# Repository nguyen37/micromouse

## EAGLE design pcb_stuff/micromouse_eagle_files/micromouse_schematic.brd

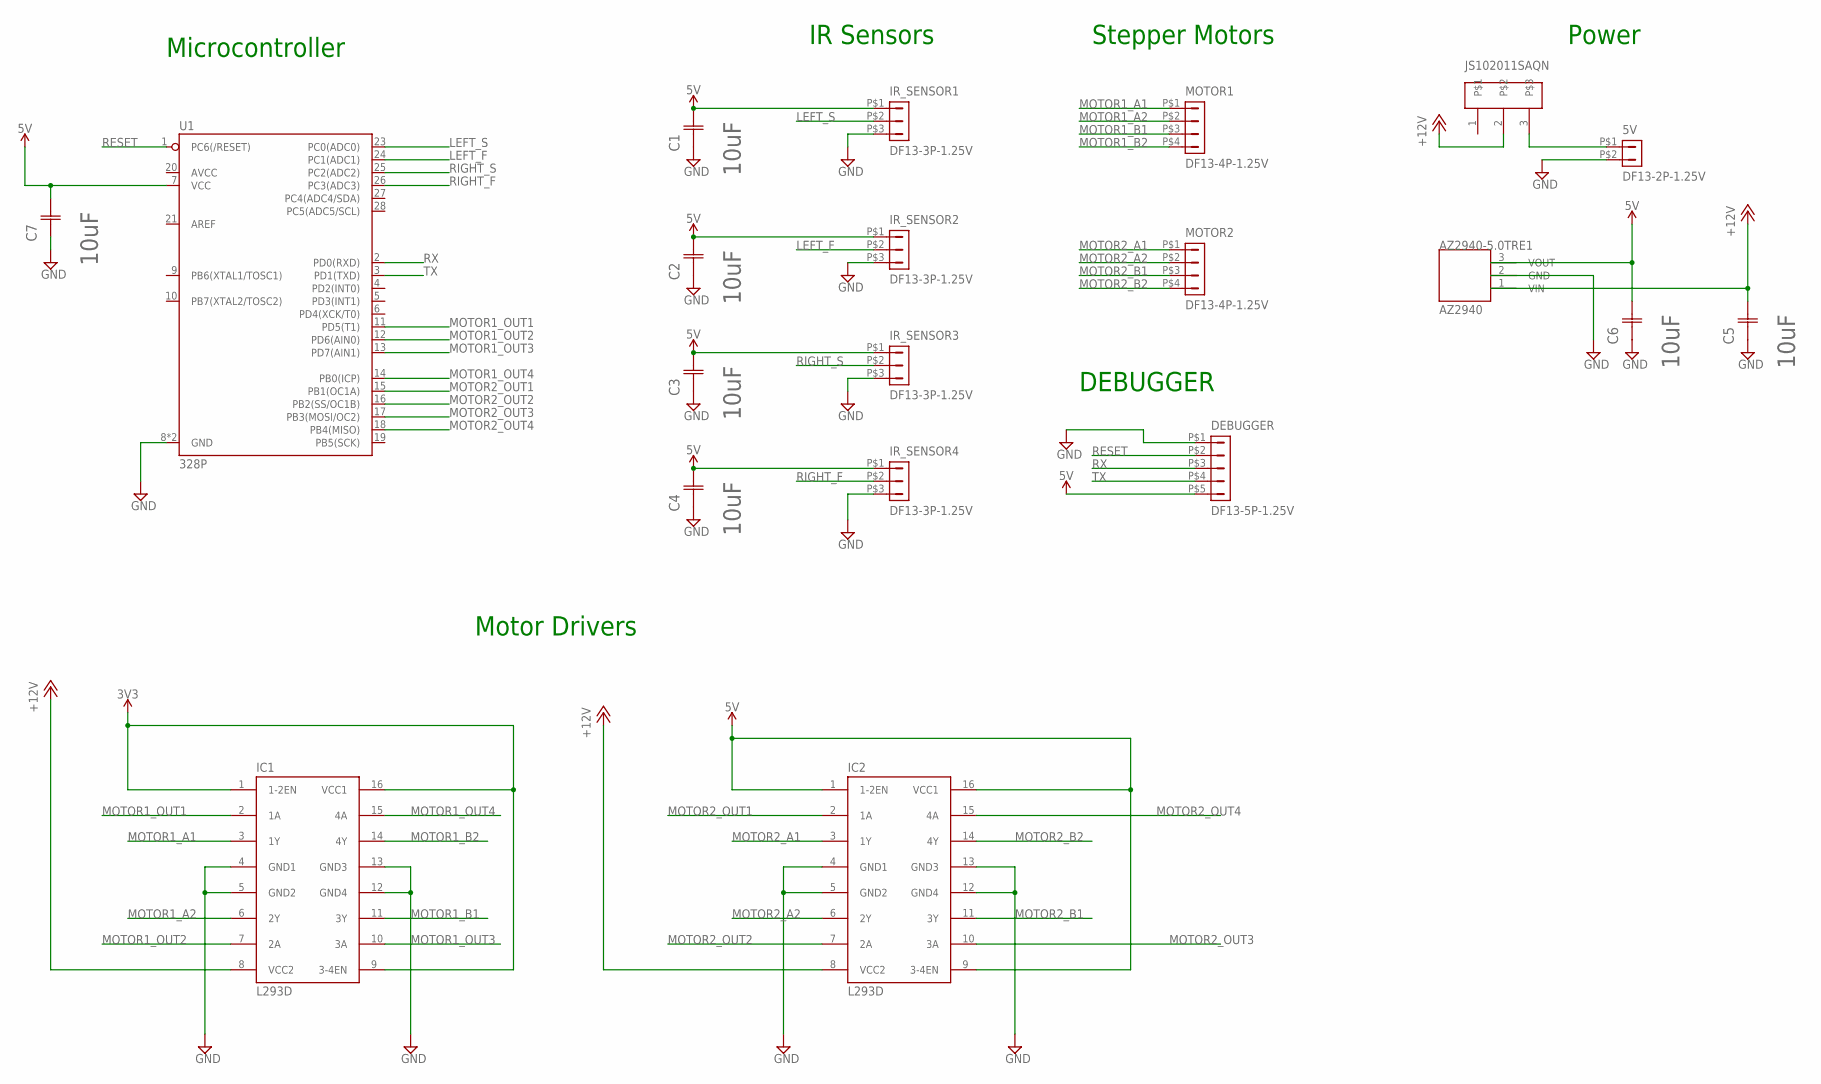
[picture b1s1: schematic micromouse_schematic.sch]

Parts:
5V: DF13-2P-1.25V; DF13C-2P-1.25V
AZ2940-5.0TRE1: AZ2940; TO-252
C1, C2, C3, C4, C5, C6, C7: 10uF; CAPC2013X135N
DEBUGGER: DF13-5P-1.25V; DF13C-5P-1.25V
IC1, IC2: L293D; DIL16
IR_SENSOR1, IR_SENSOR2, IR_SENSOR3, IR_SENSOR4: DF13-3P-1.25V; DF13C-3P-1.25V
JS102011SAQN: JS102011SAQN
MOTOR1, MOTOR2: DF13-4P-1.25V; DF13C-4P-1.25V
U1: 328P; DIP28

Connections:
+12V: AZ2940-5.0TRE1.1 (VIN), C5.2 (C2), IC1.8 (VCC2), IC2.8 (VCC2), JS102011SAQN.2
GND: 5V.P$2 (2), AZ2940-5.0TRE1.2 (GND), C1.1 (C1), C2.1 (C1), C3.1 (C1), C4.1 (C1), C5.1 (C1), C6.1 (C1), C7.1 (C1), DEBUGGER.P$1 (1), IC1.4 (GND1), IC1.5 (GND2), IC1.12 (GND4), IC1.13 (GND3), IC2.4 (GND1), IC2.5 (GND2), IC2.12 (GND4), IC2.13 (GND3), IR_SENSOR1.P$3 (3), IR_SENSOR2.P$3 (3), IR_SENSOR3.P$3 (3), IR_SENSOR4.P$3 (3), U1.8 (GND), U1.22 (GND)
LEFT_F: IR_SENSOR2.P$2 (2), U1.24 (PC1(ADC1))
LEFT_S: IR_SENSOR1.P$2 (2), U1.23 (PC0(ADC0))
MOTOR1_A1: IC1.3 (1Y), MOTOR1.P$1 (1)
MOTOR1_A2: IC1.6 (2Y), MOTOR1.P$2 (2)
MOTOR1_B1: IC1.11 (3Y), MOTOR1.P$3 (3)
MOTOR1_B2: IC1.14 (4Y), MOTOR1.P$4 (4)
MOTOR1_OUT1: IC1.2 (1A), U1.11 (PD5(T1))
MOTOR1_OUT2: IC1.7 (2A), U1.12 (PD6(AIN0))
MOTOR1_OUT3: IC1.10 (3A), U1.13 (PD7(AIN1))
MOTOR1_OUT4: IC1.15 (4A), U1.14 (PB0(ICP))
MOTOR2_A1: IC2.3 (1Y), MOTOR2.P$1 (1)
MOTOR2_A2: IC2.6 (2Y), MOTOR2.P$2 (2)
MOTOR2_B1: IC2.11 (3Y), MOTOR2.P$3 (3)
MOTOR2_B2: IC2.14 (4Y), MOTOR2.P$4 (4)
MOTOR2_OUT1: IC2.2 (1A), U1.15 (PB1(OC1A))
MOTOR2_OUT2: IC2.7 (2A), U1.16 (PB2(SS/OC1B))
MOTOR2_OUT3: IC2.10 (3A), U1.17 (PB3(MOSI/OC2))
MOTOR2_OUT4: IC2.15 (4A), U1.18 (PB4(MISO))
unnamed: 5V.P$1 (1), JS102011SAQN.3
RESET: DEBUGGER.P$2 (2), U1.1 (PC6(/RESET))
RIGHT_F: IR_SENSOR4.P$2 (2), U1.26 (PC3(ADC3))
RIGHT_S: IR_SENSOR3.P$2 (2), U1.25 (PC2(ADC2))
RX: DEBUGGER.P$3 (3), U1.2 (PD0(RXD))
TX: DEBUGGER.P$4 (4), U1.3 (PD1(TXD))
VCC: AZ2940-5.0TRE1.3 (VOUT), C1.2 (C2), C2.2 (C2), C3.2 (C2), C4.2 (C2), C6.2 (C2), C7.2 (C2), DEBUGGER.P$5 (5), IC1.1 (1-2EN), IC1.9 (3-4EN), IC1.16 (VCC1), IC2.1 (1-2EN), IC2.9 (3-4EN), IC2.16 (VCC1), IR_SENSOR1.P$1 (1), IR_SENSOR2.P$1 (1), IR_SENSOR3.P$1 (1), IR_SENSOR4.P$1 (1), U1.7 (VCC)

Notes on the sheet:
Stepper Motors
IR Sensors
DEBUGGER
Microcontroller
Motor Drivers
Power

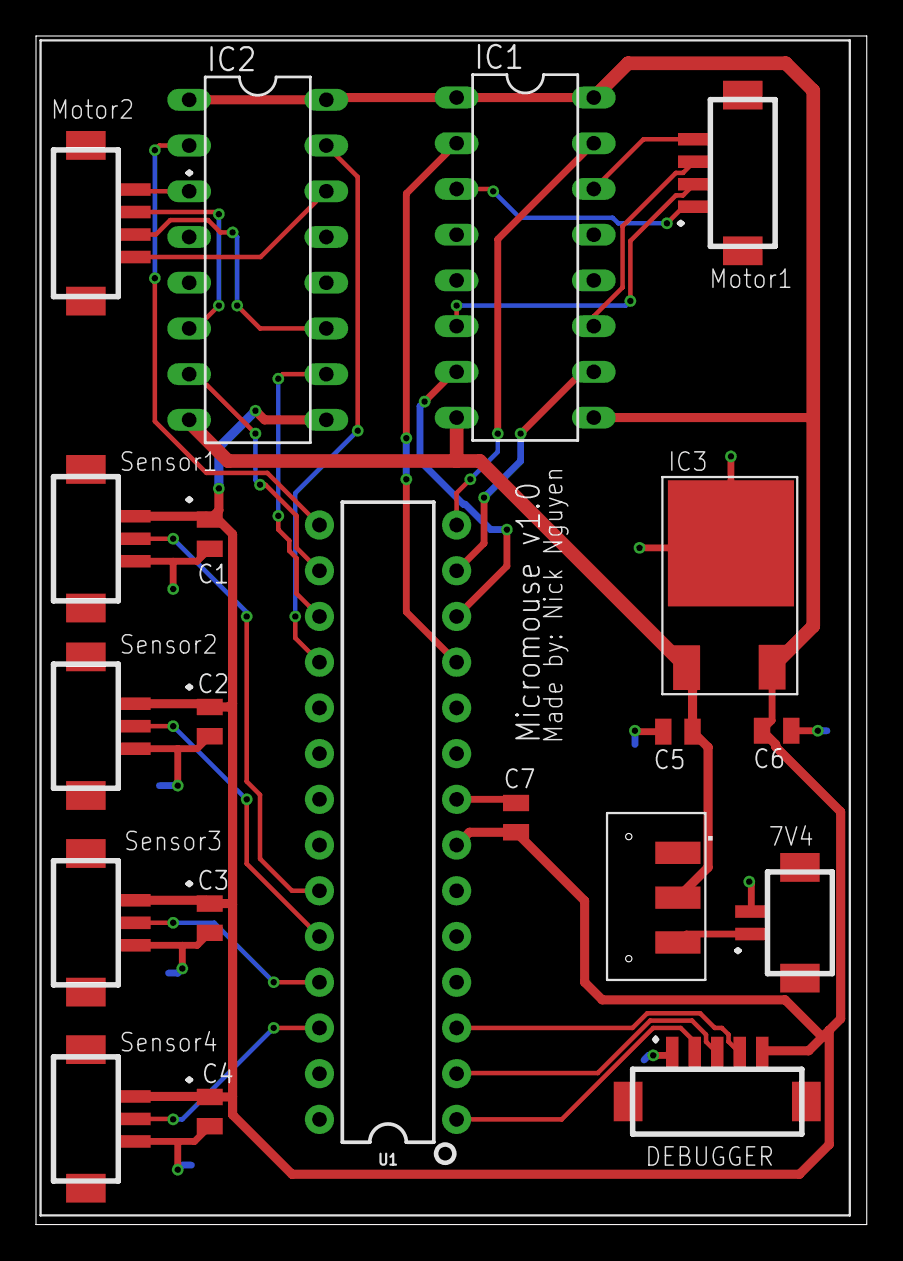
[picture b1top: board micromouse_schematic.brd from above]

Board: 2 copper layers, 46.2 x 66.0 mm, 20 parts (0 on the bottom side), 27 nets.

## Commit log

2018-02-17 added starting schematic
2018-02-19 added to micromouse schematic
2018-03-05 added gerber files and eagle files
2018-03-05 added again*

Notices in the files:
parts and their libraries:
SparkFun-IC-Microcontroller: Licensing: Creative Commons ShareAlike 4.0 International - https://creativecommons.org/licenses/by-sa/4.0
